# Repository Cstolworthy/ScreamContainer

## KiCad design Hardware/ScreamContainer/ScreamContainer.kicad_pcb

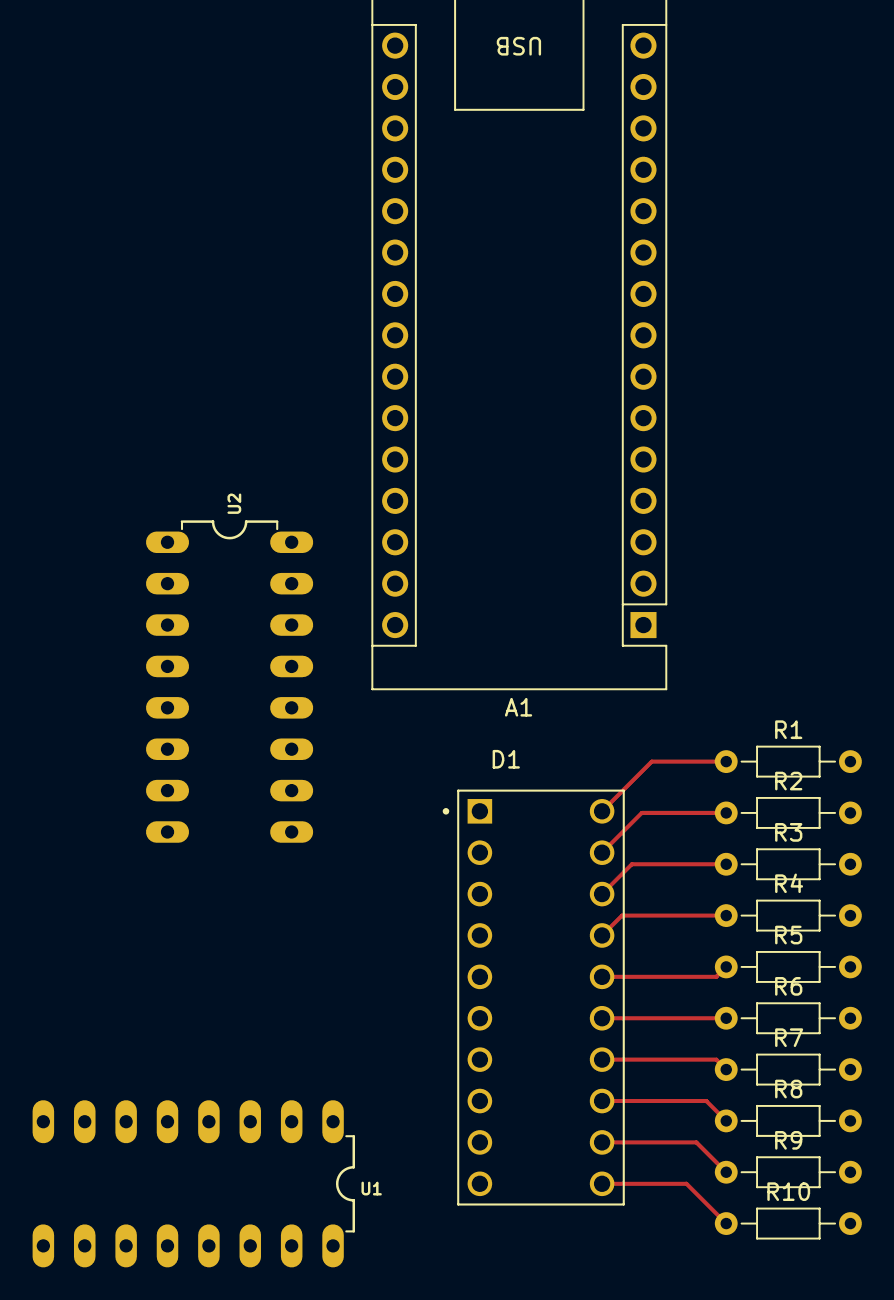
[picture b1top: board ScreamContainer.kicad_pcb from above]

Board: 2 copper layers, 14 parts (0 on the bottom side), 26 nets.

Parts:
A1: Arduino_Nano_Every; Arduino_Nano
D1: DC10EWA; DIP750W50P254L2540H825Q20
R1, R2, R3, R4, R5, R6, R7, R8, R9, R10: 220Ω; R_Axial_DIN0204_L3.6mm_D1.6mm_P7.62mm_Horizontal
U1, U2: 74HC595N-DIP16; DIP16-2.54-20.32X5.84MM

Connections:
GND: A1.4 (GND), A1.29 (GND), R1.2, R2.2, R3.2, R4.2, R5.2, R6.2, R7.2, R8.2, R9.2, R10.2, U1.8 (GND), U1.13 (G), U2.8 (GND), U2.13 (G)
unnamed: A1.11 (D8), U1.12 (RCK), U2.12 (RCK)
unnamed: A1.15 (MISO), U1.11 (SCK), U2.11 (SCK)
unnamed: A1.14 (MOSI), U1.14 (SER)
unnamed: D1.11, R10.1
unnamed: D1.12, R9.1
unnamed: D1.13, R8.1
unnamed: D1.14, R7.1
unnamed: D1.15, R6.1
unnamed: D1.16, R5.1
unnamed: D1.17, R4.1
unnamed: D1.18, R3.1
unnamed: D1.19, R2.1
unnamed: D1.20, R1.1
unnamed: D1.1, U1.15 (QA)
unnamed: D1.2, U1.1 (QB)
unnamed: D1.3, U1.2 (QC)
unnamed: D1.4, U1.3 (QD)
unnamed: D1.5, U1.4 (QE)
unnamed: D1.6, U1.5 (QF)
unnamed: D1.7, U1.6 (QG)
unnamed: D1.8, U1.7 (QH)
unnamed: U1.9 (QH*), U2.14 (SER)
unnamed: D1.9, U2.15 (QA)
unnamed: D1.10, U2.1 (QB)
VCC: A1.27 (+5V), U1.10 (SCL), U1.16 (VCC), U2.10 (SCL), U2.16 (VCC)

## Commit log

2024-05-01 Adding initial circuit design
2024-05-02 Removing some files and adding new symbols
